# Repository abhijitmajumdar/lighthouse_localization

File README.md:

# WORK IN PROGRESS

## Usage
#### Upload code onto sensor interface board
The PCB design files for the sensor interface board are in the `sensor_interface_board` directory. Once the board is populated with the components, please refer to the [Readme](sensor_interface/README.md) in the `sensor_interface` directory for instructions on connecting this to a processor board (I use a [NanoPi Duo](http://wiki.friendlyarm.com/wiki/index.php/NanoPi_Duo)).
Please refer to the same [Readme](sensor_interface/README.md) for instructions on uploading the C code onto the board.

Uploading the program onto the board connected to a processor board should be as simple as follows(assuming all dependencies have been installed as indicated in the [Readme](sensor_interface/README.md) file)(also assuming connection is made over `/dev/ttyS1` serial interface)
```
cd sensor_interface
make -j
USB_DEVICE=/dev/ttyS1 make upload
```
For any issues please refer [Readme](sensor_interface/README.md)

#### Running the positioning program
By default, the program publishes the pose over ROS. Make sure a ROS master is properly configured (ideally to a remote computer, to be able to visualize the pose and transforms on RViz). Run the following command in the root directory
```
python run.py
```

To record the pose data while running, use following flag(*data* is the filename to save pose data in)
```
python run.py -r data
```

To view the saved data, use the following command (Note: If running the plot command on the device over a remote SSH connection, make sure the `-X` flag is enabled to view the plot)
```
python run.py -plot data.npy
```

If the connected sensor interface board is on a different dev port (say /dev/ttyUSB0), use the following flag
```
python run.py -p /dev/ttyUSB0
```

For more options to run the program look up help
```
python run.py -h
```

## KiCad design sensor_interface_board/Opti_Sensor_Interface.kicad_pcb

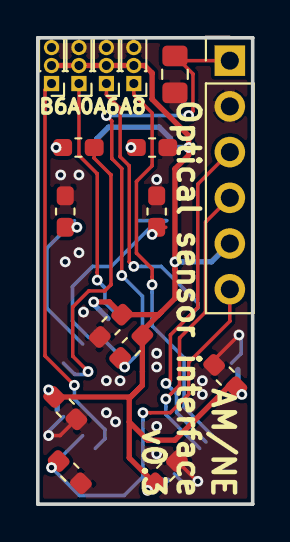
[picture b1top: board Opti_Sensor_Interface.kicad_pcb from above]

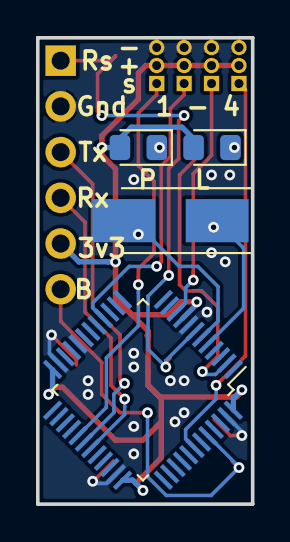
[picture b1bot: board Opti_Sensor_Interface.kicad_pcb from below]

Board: 2 copper layers, 11.9 x 25.9 mm, 20 parts (4 on the bottom side), 15 nets.

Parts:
C1, C2: 22 pF; C_0603_1608Metric_Pad1.05x0.95mm_HandSolder
C3: 1uF; C_0805_2012Metric_Pad1.15x1.40mm_HandSolder
C9, C24, C36, C48: 100nF; C_0603_1608Metric_Pad1.05x0.95mm_HandSolder
D1, D2: LED; LED_0805_2012Metric_Pad1.15x1.40mm_HandSolder
J1, J3, J4, J5: Conn_01x03_Male; PinHeader_1x03_P1.00mm_Vertical
J2: Conn_01x06_Male; PinHeader_1x06_P2.54mm_Vertical
R1: 100K; R_0603_1608Metric_Pad1.05x0.95mm_HandSolder
R2: 10K; R_0603_1608Metric_Pad1.05x0.95mm_HandSolder
R3, R4: 510; R_0603_1608Metric_Pad1.05x0.95mm_HandSolder
U1: STM32F103C8Tx; LQFP-48_7x7mm_P0.5mm
Y2: Crystal; Crystal_SMD_5032-2Pin_5.0x3.2mm_HandSoldering

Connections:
+3V3: C9.2, C24.2, C36.2, C48.2, D1.2, D2.2, J1.2, J2.5, J3.2, J4.2, J5.2, R2.2, U1.9, U1.24, U1.36, U1.48
BOOT0: J2.6, R1.1, U1.44
GND: C1.1, C2.2, C3.1, C9.1, C24.1, C36.1, C48.1, J1.3, J2.2, J3.3, J4.3, J5.3, R1.2, R3.1, U1.8, U1.20, U1.23, U1.35, U1.47
unnamed: C1.2, U1.5, Y2.1
unnamed: C2.1, U1.6, Y2.2
unnamed: D1.1, R3.2
unnamed: D2.1, R4.2
PA0: J3.1, U1.10
PA6: J4.1, U1.16
PA8: J5.1, U1.29
PB6: J1.1, U1.42
PC13: R4.1, U1.2
RST: C3.2, J2.1, R2.1, U1.7
RX: J2.4, U1.31
TX: J2.3, U1.30

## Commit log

2018-09-17 tested and working
2018-09-18 memory overwrite fix
2018-09-18 bluepill connected to nano pi
2018-09-22 different type of delays and configurable default delay
2018-09-23 working angle inference for single sensor
2018-09-25 working with timer 2 and 4, need chages for 1, cannot work with 3
2018-09-27 3 sensors woking with positions and resolutions, with ootx decoded using 1
2018-10-08 request to get data now, minor fixes
2018-10-09 working 4 sensors with interrupts and buffer, with ootx decoding
2019-01-20 use DEBUG=true/false as make argument
2019-01-20 reorganizing
2019-01-21 modularized, added scripts to run on processor, and communication interfaces
2019-01-21 added recording and plotting pose data, added design files for sensor interface board pcb and renders
2019-01-21 added some information in the readme to get things running
2019-01-21 linked the other readme
2019-03-08 initial changes to enable ROS with nodes and launch files
